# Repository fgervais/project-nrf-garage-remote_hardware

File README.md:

# Garage Door Interface

<a href="https://oshpark.com/shared_projects/lxWmlYXx"></img></a>

## Schematic

## PCB

## 3D Render

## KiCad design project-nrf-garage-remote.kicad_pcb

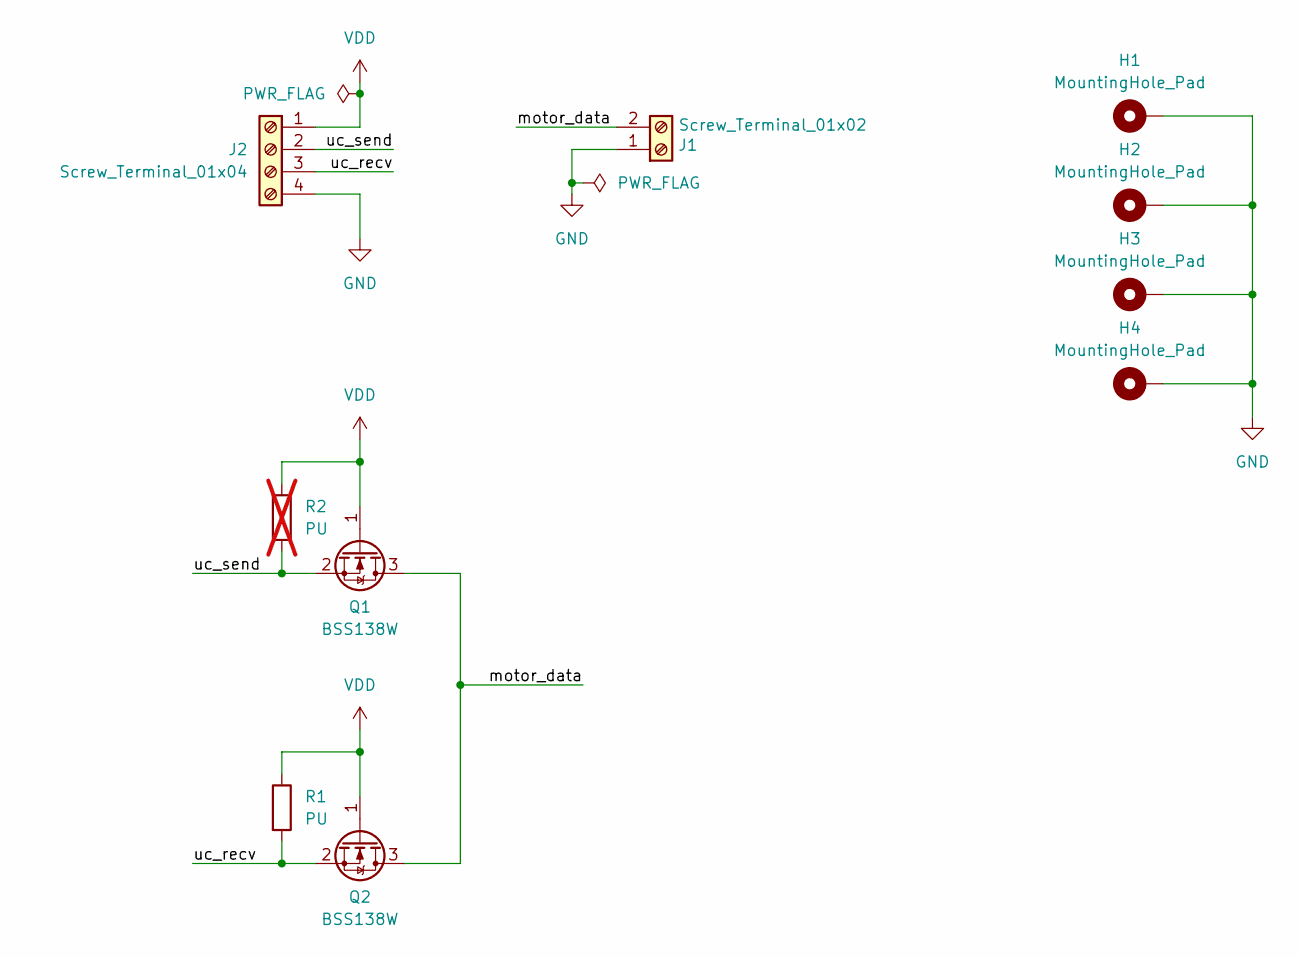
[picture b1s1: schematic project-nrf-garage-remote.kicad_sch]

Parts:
H1, H2, H3, H4: MountingHole_Pad; MountingHole_2.2mm_M2_ISO14580_Pad
J1: Screw_Terminal_01x02; TZ022101B000G
J2: Screw_Terminal_01x04; TZ042101B000G
Q1, Q2: BSS138W
R1: PU; R_0603_1608Metric
R2: PU; R_0603_1608Metric; not fitted

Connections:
/motor_data: J1.2, Q1.3 (D), Q2.3 (D)
/uc_recv: J2.3, Q2.2 (S), R1.2
/uc_send: J2.2, Q1.2 (S), R2.2
GND: H1.1, H2.1, H3.1, H4.1, J1.1, J2.4
VDD: J2.1, Q1.1 (G), Q2.1 (G), R1.1, R2.1

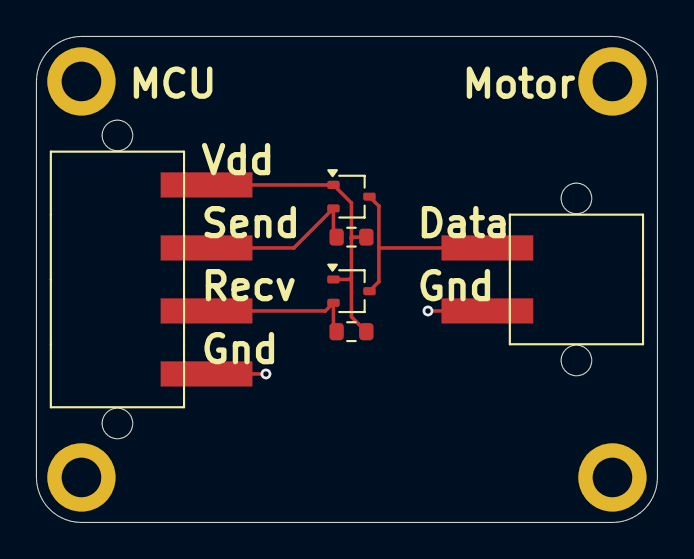
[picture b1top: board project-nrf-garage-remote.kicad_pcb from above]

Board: 2 copper layers, 34.5 x 27.0 mm, 10 parts (0 on the bottom side), 5 nets.

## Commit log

2024-10-14 Add components to schematic
2024-10-14 Connect schematic
2024-10-14 Swap mosfet symbols
2024-10-15 Add footprint to mounting holes
2024-10-15 Started board placement
2024-10-15 Change the terminals footprint
2024-10-15 Update gitignore
2024-10-15 Place parts
2024-10-15 Add silkscreen
2024-10-15 Add board outline
2024-10-16 Add routing
2024-10-16 Populate fab layer
2024-10-16 Update DRC exclusions
2024-10-17 Update schematic
2024-10-17 Update pcb
2024-10-17 Update images
2024-10-18 Set do not populate part
2024-10-18 Add OSH Park link
